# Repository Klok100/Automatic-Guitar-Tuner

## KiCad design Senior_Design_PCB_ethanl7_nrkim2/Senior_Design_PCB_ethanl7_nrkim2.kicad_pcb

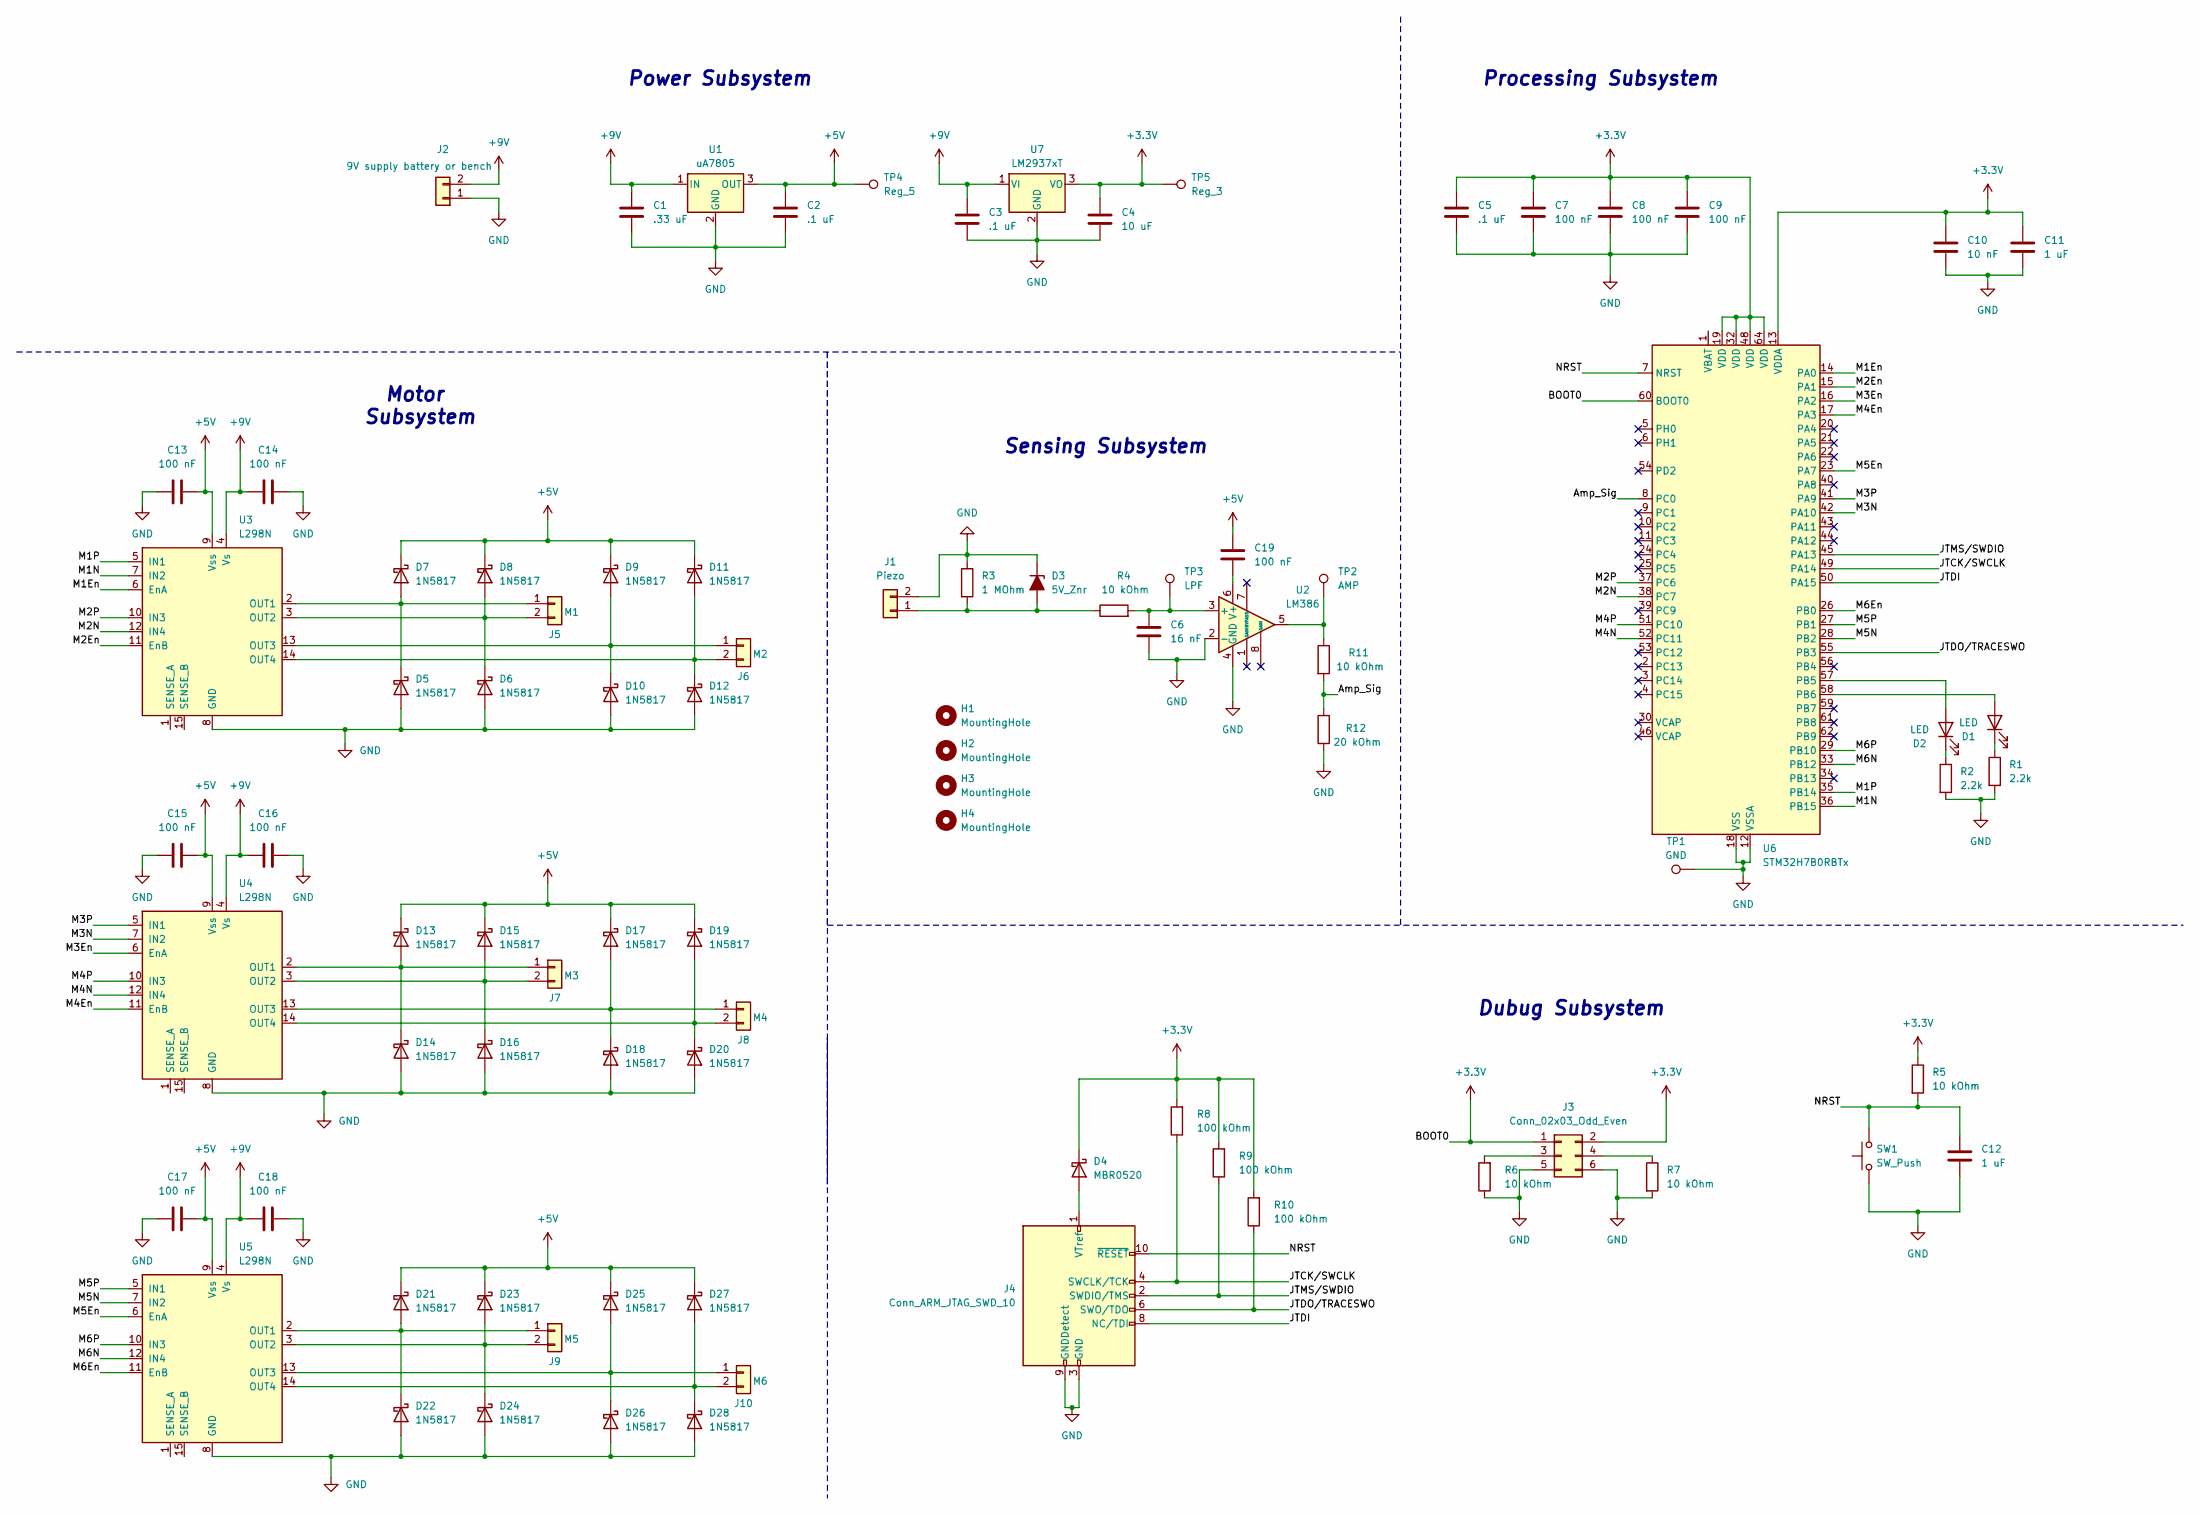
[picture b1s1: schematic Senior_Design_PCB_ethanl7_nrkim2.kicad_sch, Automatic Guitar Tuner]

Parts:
C1: .33 uF; C_0805_2012Metric_Pad1.18x1.45mm_HandSolder
C2, C3, C5: .1 uF; C_0805_2012Metric_Pad1.18x1.45mm_HandSolder
C4: 10 uF; C_0805_2012Metric_Pad1.18x1.45mm_HandSolder
C6: 16 nF; C_0805_2012Metric_Pad1.18x1.45mm_HandSolder
C7, C8, C9, C13, C14, C15, C16, C17, C18, C19: 100 nF; C_0805_2012Metric_Pad1.18x1.45mm_HandSolder
C10: 10 nF; C_0805_2012Metric_Pad1.18x1.45mm_HandSolder
C11, C12: 1 uF; C_0805_2012Metric_Pad1.18x1.45mm_HandSolder
D1, D2: LED; Molex_KK-254_AE-6410-02A_1x02_P2.54mm_Vertical
D3: 5V_Znr; D_DO-41_SOD81_P10.16mm_Horizontal
D4: MBR0520; D_SOD-123
D5, D6, D7, D8, D9, D10, D11, D12, D13, D14, D15, D16, D17, D18, D19, D20, D21, D22, D23, D24, D25, D26, D27, D28: 1N5817; D_DO-41_SOD81_P10.16mm_Horizontal
H1, H2, H3, H4: MountingHole; MountingHole_3.2mm_M3
J1: Piezo; Molex_KK-254_AE-6410-02A_1x02_P2.54mm_Vertical
J2: 9V supply battery or bench; Molex_KK-254_AE-6410-02A_1x02_P2.54mm_Vertical
J3: Conn_02x03_Odd_Even; PinSocket_2x03_P2.54mm_Vertical
J4: Conn_ARM_JTAG_SWD_10; IDC-Header_2x05_P2.54mm_Vertical
J5: M1; Molex_KK-254_AE-6410-02A_1x02_P2.54mm_Vertical
J6: M2; Molex_KK-254_AE-6410-02A_1x02_P2.54mm_Vertical
J7: M3; Molex_KK-254_AE-6410-02A_1x02_P2.54mm_Vertical
J8: M4; Molex_KK-254_AE-6410-02A_1x02_P2.54mm_Vertical
J9: M5; Molex_KK-254_AE-6410-02A_1x02_P2.54mm_Vertical
J10: M6; Molex_KK-254_AE-6410-02A_1x02_P2.54mm_Vertical
R1, R2: 2.2k; R_0805_2012Metric_Pad1.20x1.40mm_HandSolder
R3: 1 MOhm; R_0805_2012Metric_Pad1.20x1.40mm_HandSolder
R4, R5, R6, R7, R11: 10 kOhm; R_0805_2012Metric_Pad1.20x1.40mm_HandSolder
R8, R9, R10: 100 kOhm; R_0805_2012Metric_Pad1.20x1.40mm_HandSolder
R12: 20 kOhm; R_0805_2012Metric_Pad1.20x1.40mm_HandSolder
SW1: SW_Push; SW_SPST_B3S-1000
TP1: GND; TestPoint_Pad_D1.5mm
TP2: AMP; TestPoint_Pad_D1.5mm
TP3: LPF; TestPoint_Pad_D1.5mm
TP4: Reg_5; TestPoint_Pad_D1.5mm
TP5: Reg_3; TestPoint_Pad_D1.5mm
U1: uA7805; TO-220-3_Vertical
U2: LM386; DIP-8_W7.62mm
U3, U4, U5: L298N; TO-220-15_P2.54x2.54mm_StaggerOdd_Lead4.58mm_Vertical
U6: STM32H7B0RBTx; LQFP-64_10x10mm_P0.5mm
U7: LM2937xT; TO-220-3_Vertical

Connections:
+3.3V: C4.1, C5.1, C7.1, C8.1, C9.1, C10.1, C11.1, D4.1 (K), J3.1, J3.2, R5.1, R8.2, R9.2, R10.2, TP5.1, U6.13 (VDDA), U6.19 (VDD), U6.32 (VDD), U6.48 (VDD), U6.60 (BOOT0), U6.64 (VDD), U7.3 (VO)
+5V: C2.1, C13.2, C15.2, C17.2, C19.2, D7.1 (K), D8.1 (K), D9.1 (K), D11.1 (K), D13.1 (K), D15.1 (K), D17.1 (K), D19.1 (K), D21.1 (K), D23.1 (K), D25.1 (K), D27.1 (K), TP4.1, U1.3 (OUT), U3.9 (Vss), U4.9 (Vss), U5.9 (Vss)
+9V: C1.1, C3.1, C14.1, C16.1, C18.1, J2.2, U1.1 (IN), U3.4 (Vs), U4.4 (Vs), U5.4 (Vs), U7.1 (VI)
/Amp_Sig: R11.2, R12.2, U6.8 (PC0)
/JTCK/SWCLK: J4.4 (SWCLK/TCK), R8.1, U6.49 (PA14)
/JTDI: J4.8 (NC/TDI), U6.50 (PA15)
/JTDO/TRACESWO: J4.6 (SWO/TDO), R10.1, U6.55 (PB3)
/JTMS/SWDIO: J4.2 (SWDIO/TMS), R9.1, U6.45 (PA13)
/M1En: U3.6 (EnA), U6.14 (PA0)
/M1N: U3.7 (IN2), U6.36 (PB15)
/M1P: U3.5 (IN1), U6.35 (PB14)
/M2En: U3.11 (EnB), U6.15 (PA1)
/M2N: U3.12 (IN4), U6.38 (PC7)
/M2P: U3.10 (IN3), U6.37 (PC6)
/M3En: U4.6 (EnA), U6.16 (PA2)
/M3N: U4.7 (IN2), U6.42 (PA10)
/M3P: U4.5 (IN1), U6.41 (PA9)
/M4En: U4.11 (EnB), U6.17 (PA3)
/M4N: U4.12 (IN4), U6.52 (PC11)
/M4P: U4.10 (IN3), U6.51 (PC10)
/M5En: U5.6 (EnA), U6.23 (PA7)
/M5N: U5.7 (IN2), U6.28 (PB2)
/M5P: U5.5 (IN1), U6.27 (PB1)
/M6En: U5.11 (EnB), U6.26 (PB0)
/M6N: U5.12 (IN4), U6.33 (PB12)
/M6P: U5.10 (IN3), U6.29 (PB10)
/NRST: C12.1, J4.10 (~RESET), R5.2, SW1.2, U6.7 (NRST)
GND: C1.2, C2.2, C3.2, C4.2, C5.2, C6.1, C7.2, C8.2, C9.2, C10.2, C11.2, C12.2, C13.1, C14.2, C15.1, C16.2, C17.1, C18.2, D3.1 (K), D5.2 (A), D6.2 (A), D10.2 (A), D12.2 (A), D14.2 (A), D16.2 (A), D18.2 (A), D20.2 (A), D22.2 (A), D24.2 (A), D26.2 (A), D28.2 (A), J1.2, J2.1, J3.5, J3.6, J4.3 (GND), J4.5 (GND), J4.9 (GNDDetect), R1.2, R2.2, R3.1, R6.1, R7.2, R12.1, SW1.1, TP1.1, U1.2 (GND), U2.2 (-), U2.4 (GND), U3.8 (GND), U4.8 (GND), U5.8 (GND), U6.12 (VSSA), U6.18 (VSS), U6.31 (VSS), U6.47 (VSS), U6.63 (VSS), U7.2 (GND)
unnamed: D1.2 (A), U6.58 (PB6)
unnamed: D1.1 (K), R1.1
unnamed: D2.2 (A), U6.57 (PB5)
unnamed: D2.1 (K), R2.1
unnamed: D3.2 (A), J1.1, R3.2, R4.1
unnamed: D4.2 (A), J4.1 (VTref)
unnamed: D5.1 (K), D7.2 (A), J5.1, U3.2 (OUT1)
unnamed: D6.1 (K), D8.2 (A), J5.2, U3.3 (OUT2)
unnamed: D9.2 (A), D10.1 (K), J6.1, U3.13 (OUT3)
unnamed: D11.2 (A), D12.1 (K), J6.2, U3.14 (OUT4)
unnamed: D13.2 (A), D14.1 (K), J7.1, U4.2 (OUT1)
unnamed: D15.2 (A), D16.1 (K), J7.2, U4.3 (OUT2)
unnamed: D17.2 (A), D18.1 (K), J8.1, U4.13 (OUT3)
unnamed: D19.2 (A), D20.1 (K), J8.2, U4.14 (OUT4)
unnamed: D21.2 (A), D22.1 (K), J9.1, U5.2 (OUT1)
unnamed: D23.2 (A), D24.1 (K), J9.2, U5.3 (OUT2)
unnamed: D25.2 (A), D26.1 (K), J10.1, U5.13 (OUT3)
unnamed: D27.2 (A), D28.1 (K), J10.2, U5.14 (OUT4)
unnamed: J3.3, R6.2
unnamed: J3.4, R7.1
unnamed: R11.1, TP2.1, U2.5
unnamed: C6.2, R4.2, TP3.1, U2.3 (+)
unnamed: C19.1, U2.6 (V+)

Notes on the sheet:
Power Subsystem
Processing Subsystem
Sensing Subsystem
Dubug Subsystem
Motor Subsystem

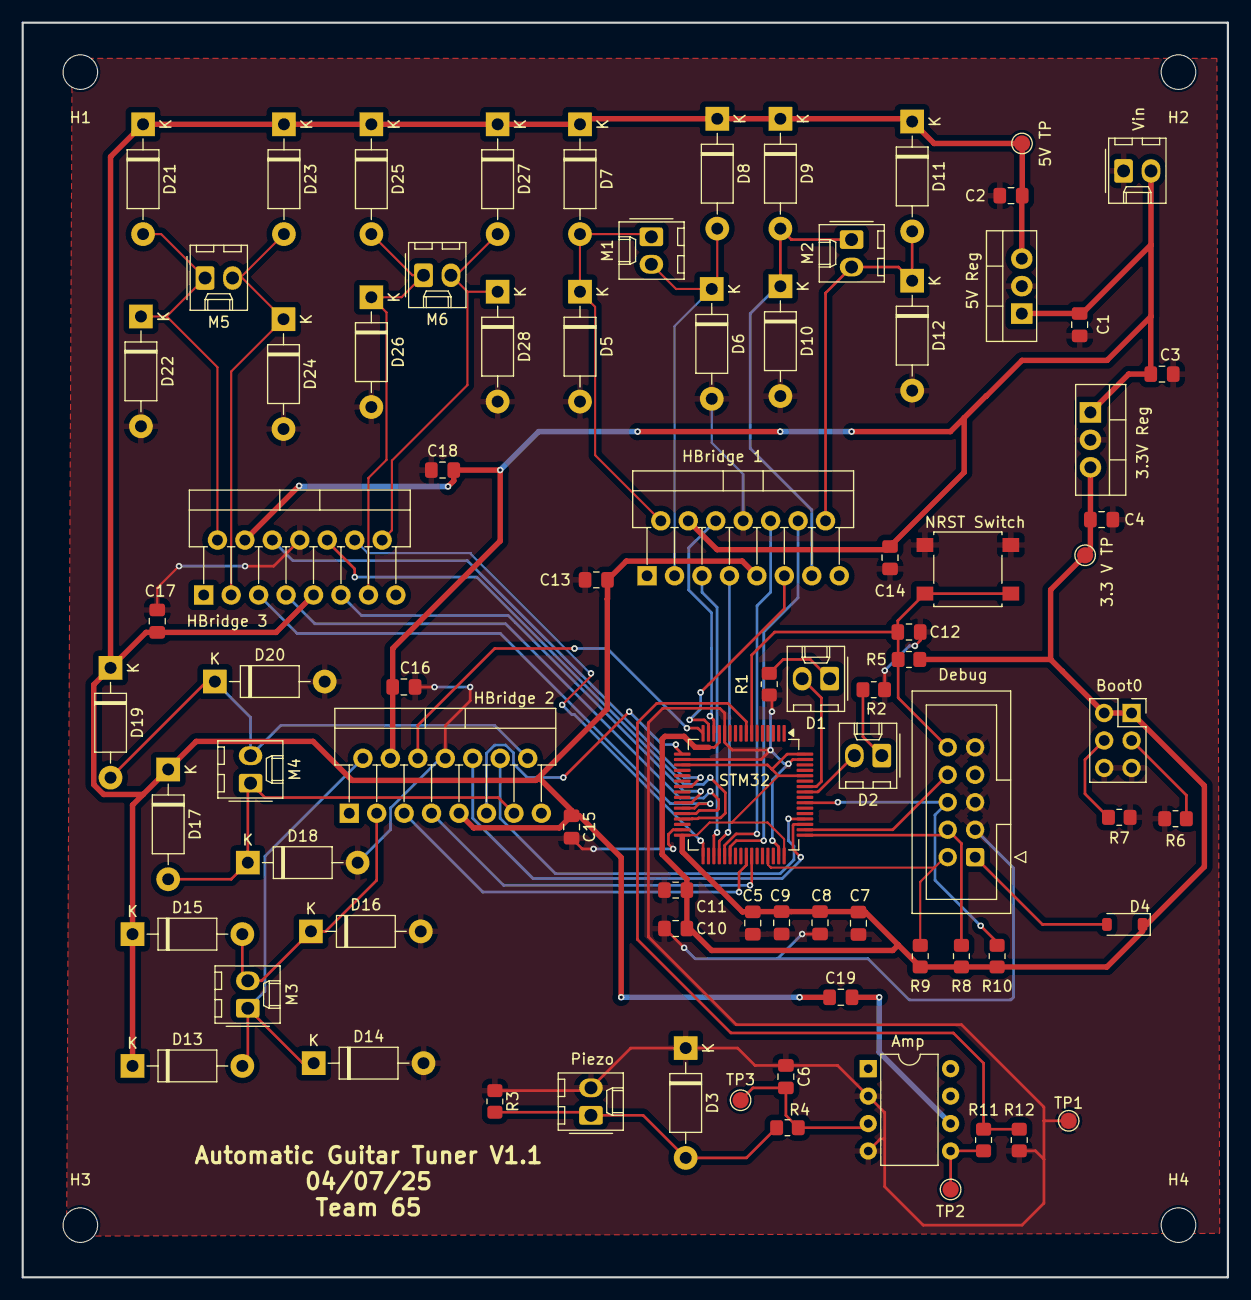
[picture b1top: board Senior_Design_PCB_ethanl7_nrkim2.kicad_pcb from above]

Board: 2 copper layers, 111.5 x 116.1 mm, 86 parts (0 on the bottom side), 51 nets.

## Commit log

2025-02-11 Basic Setup Nathan-Lab-Notebook.md
2025-02-12 Update Ethan-Lab-Notebook.md
    added notes for 2.11 first TA meeting
2025-02-12 Update Ethan-Lab-Notebook.md
    added link for model block diagram from TA
2025-02-14 Added Project Proposal and Initial Team Contract
2025-02-15 Updated Team Contract
2025-02-17 Update Ethan-Lab-Notebook.md
    added high level process overview pre Design Review
2025-02-17 Update Ethan-Lab-Notebook.md
    peer design review notes
2025-02-19 Updated Project Proposal and Team Contract
2025-02-27 Update 3.3 Voltage Regulator
2025-02-27 Added 5V Regulator
2025-02-28 Added KiCad Files
2025-02-28 Update Senior-Design-Parts.md
    Update parts with datasheets and links according to new needs during schematic design process
2025-02-28 added linear regulator analysis, editable doc in GDrive
2025-02-28 changes to schematic
2025-02-28 add backing files for schematic
2025-02-28 schematic power supply and sensing
2025-03-04 Update Ethan-Lab-Notebook.md
    added 3d printing info
2025-03-05 added 3d printing files
2025-03-06 increased part sizes of 3d print files
2025-03-06 motor shaft sizing 3d print file
2025-03-06 Update Senior-Design-Parts.md
    changed which vendor we were going through
2025-03-06 added stl for shaft sizing part
2025-03-06 new shaft sizing on main part and new mini part for testing
2025-03-06 adjust tuning peg to motor connection
2025-03-06 Update Ethan-Lab-Notebook.md
    TA meeting 3.6
2025-03-06 Added Example Project Report
2025-03-07 Added Design Document
2025-03-11 scopy spectrogram data, slight updates to magnet mount and PCB schematic
2025-03-11 Started Microcontroller Code
2025-03-11 out of tune spectrogram added
2025-03-11 Started Python Frequency Analysis
2025-03-11 magnet mount stl
2025-03-18 schematic updates
2025-03-18 added fillet to base of magnet mount
2025-03-26 Updated Weeks 1-4.md
2025-03-27 Updated Weeks 5-8
2025-03-27 made mgnet mount shorter
2025-03-27 Updated Helpful Links (Datasheets)
2025-03-30 Update Senior-Design-Parts.md
    Added Zener
2025-03-30 finished schematic, started pcb
2025-04-02 finished v1 pcb design
2025-04-02 added out of tune scopy and dims on part files
2025-04-02 Cleaned up Python Script
2025-04-03 tweaked PCB layout
2025-04-08 V1.1 pcb
2025-04-09 Updated Helpful Links
2025-04-14 PCB updates, new motor tuning peg for worm motor, new motor part file for 3d modeling purposes
2025-04-15 enlarged tuning peg hole by 1mm, created assembly and parts for full 3d model
2025-04-16 created guitar 3d model for full 3d model, started assembly of full 3d model
2025-04-17 more 3d model parts and updated assembly
2025-04-19 added more 3d model parts
2025-04-21 stl files for 3d printing
2025-04-23 Update Ethan-Lab-Notebook.md
    formatting
2025-04-23 Update Senior-Design-Parts.md
    part locations
2025-05-08 Updated Weeks 10-12
2025-05-08 Updated Week 12
2025-05-08 PCB and 3D printed final parts and version
2025-05-08 Updated Weeks 13-14.5
2025-05-08 bones
2025-05-08 Update Ethan-Lab-Notebook.md
    Filled out
2025-05-08 Update Ethan-Lab-Notebook.md
    Flesh
2025-05-08 Update Ethan-Lab-Notebook.md
    minor adds
2025-05-08 Update Ethan-Lab-Notebook.md
    added eqs and ims
2025-05-08 pcb no changes
2025-05-08 more depth on all notebook
2025-05-08 formatting
2025-05-08 Update Ethan-Lab-Notebook.md
    added images
2025-05-08 Updated Weeks 14-15.5
2025-05-09 Updated Week 15-16
2025-05-09 Commit files for merge
2025-05-09 Updated All Microcontroller Code
